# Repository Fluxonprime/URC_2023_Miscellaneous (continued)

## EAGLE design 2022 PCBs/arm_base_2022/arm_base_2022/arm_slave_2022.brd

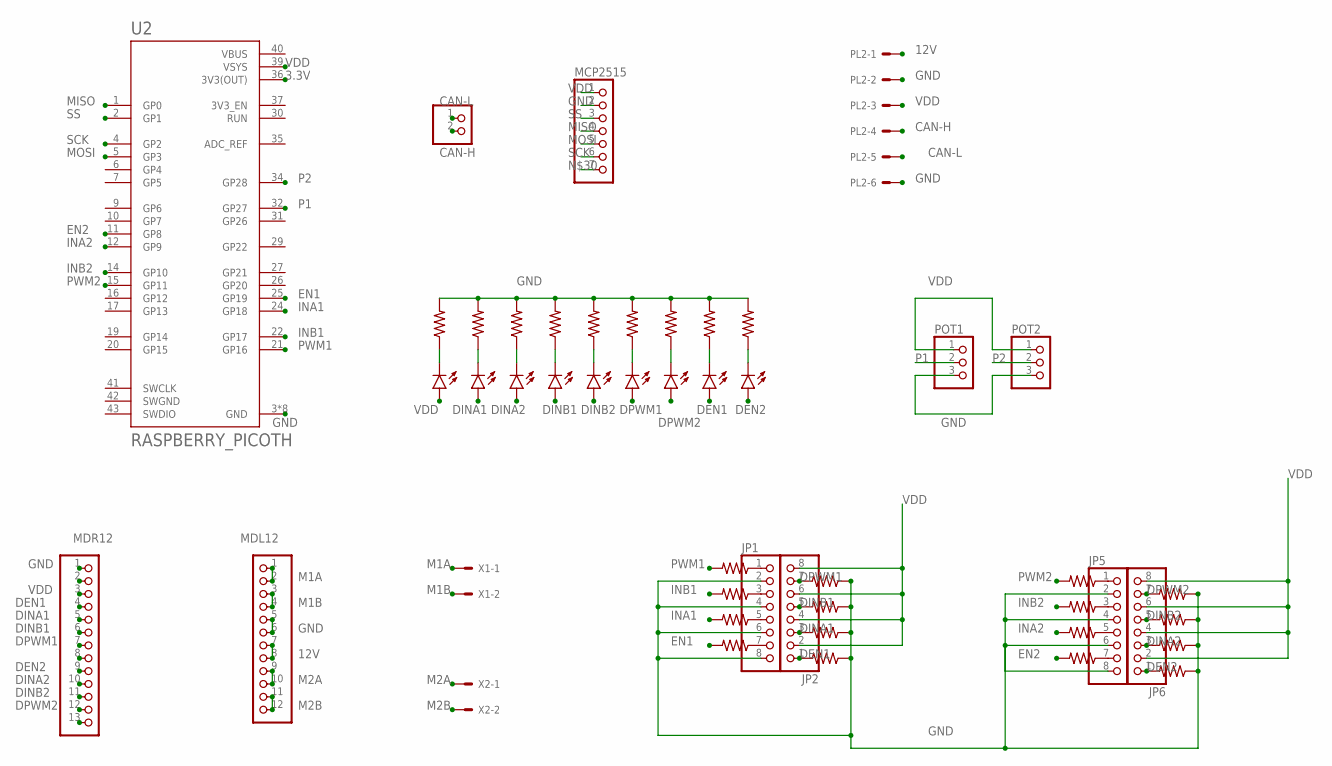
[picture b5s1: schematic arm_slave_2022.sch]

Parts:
CAN_L: CAN_H; 1X02
EN1, EN2: LEDSMT1206; 1206
INA1, INA2: LEDSMT1206; 1206
INB1, INB2: LEDSMT1206; 1206
JP1, JP2, JP5, JP6: PINHD-1X8BIG; 1X08-BIG
MCP2515: PINHD-1X7; 1X07
MDL: MDL12; 1X12
MDR: MDR12; 1X13
PL2: 555X-6V; 5566-6
POT1, POT2: PINHD-1X3; 1X03
PWM1, PWM2: LEDSMT1206; 1206
R3, R4, R5, R6, R9, R11, R14, R15, R16, R17, R18, R19, R20, R33, R34, R56, R58, R59, R60, R61, R62, R63, R64, R65, R66: R-US_R0805; R0805
U2: RASPBERRY_PICOTH; PICO-PKG-TH
VDD: LEDSMT1206; 1206
X1, X2: KK-156-2

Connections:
3.3V: U2.36 (3V3(OUT))
12V: MDL.7, MDL.8, PL2.1
CAN-H: CAN_L.2, PL2.4
CAN-L: CAN_L.1, PL2.5
DEN1: EN1.A, JP2.1, MDR.4, R11.2
DEN2: EN2.A, JP6.1, MDR.9, R58.2
DINA1: INA1.A, JP2.3, MDR.5, R4.2
DINA2: INA2.A, JP6.3, MDR.10, R6.2
DINB1: INB1.A, JP2.5, MDR.6, R9.2
DINB2: INB2.A, JP6.5, MDR.11, R56.2
DPWM1: JP2.7, MDR.7, PWM1.A, R3.2
DPWM2: JP6.7, MDR.12, PWM2.A, R5.2
EN1: R62.2, U2.25 (GP19)
EN2: R66.2, U2.11 (GP8)
GND: JP1.2, JP1.4, JP1.6, JP1.8, JP5.2, JP5.4, JP5.6, JP5.8, MCP2515.2, MDL.5, MDL.6, MDR.1, PL2.2, PL2.6, POT1.3, POT2.3, R3.1, R5.1, R14.2, R15.2, R16.2, R17.2, R18.2, R19.2, R20.2, R33.2, R34.2, U2.3 (GND), U2.8 (GND), U2.13 (GND), U2.18 (GND), U2.23 (GND), U2.28 (GND), U2.33 (GND), U2.38 (GND)
INA1: R61.2, U2.24 (GP18)
INA2: R65.2, U2.12 (GP9)
INB1: R60.2, U2.22 (GP17)
INB2: R64.2, U2.14 (GP10)
M1A: MDL.1, MDL.2, X1.1
M1B: MDL.3, MDL.4, X1.2
M2A: MDL.9, MDL.10, X2.1
M2B: MDL.11, MDL.12, X2.2
MISO: MCP2515.4, U2.1 (GP0)
MOSI: MCP2515.5, U2.5 (GP3)
unnamed: INA1.C, R15.1
unnamed: INA2.C, R16.1
unnamed: INB1.C, R17.1
unnamed: R14.1, VDD.C
unnamed: INB2.C, R18.1
unnamed: PWM1.C, R19.1
unnamed: PWM2.C, R20.1
unnamed: EN1.C, R33.1
unnamed: EN2.C, R34.1
unnamed: JP1.1, R59.1
unnamed: JP1.3, R60.1
unnamed: JP1.5, R61.1
unnamed: JP1.7, R62.1
unnamed: JP5.1, R63.1
unnamed: JP5.3, R64.1
unnamed: JP5.5, R65.1
unnamed: JP5.7, R66.1
P1: POT1.2, U2.32 (GP27)
P2: POT2.2, U2.34 (GP28)
PWM1: R59.2, U2.21 (GP16)
PWM2: R63.2, U2.15 (GP11)
SCK: MCP2515.6, U2.4 (GP2)
SS: MCP2515.3, U2.2 (GP1)
SWGND: U2.42 (SWGND)
VBUS: U2.40 (VBUS)
VDD: JP2.2, JP2.4, JP2.6, JP2.8, JP6.2, JP6.4, JP6.6, JP6.8, MCP2515.1, MDR.3, PL2.3, POT1.1, POT2.1, U2.39 (VSYS), VDD.A

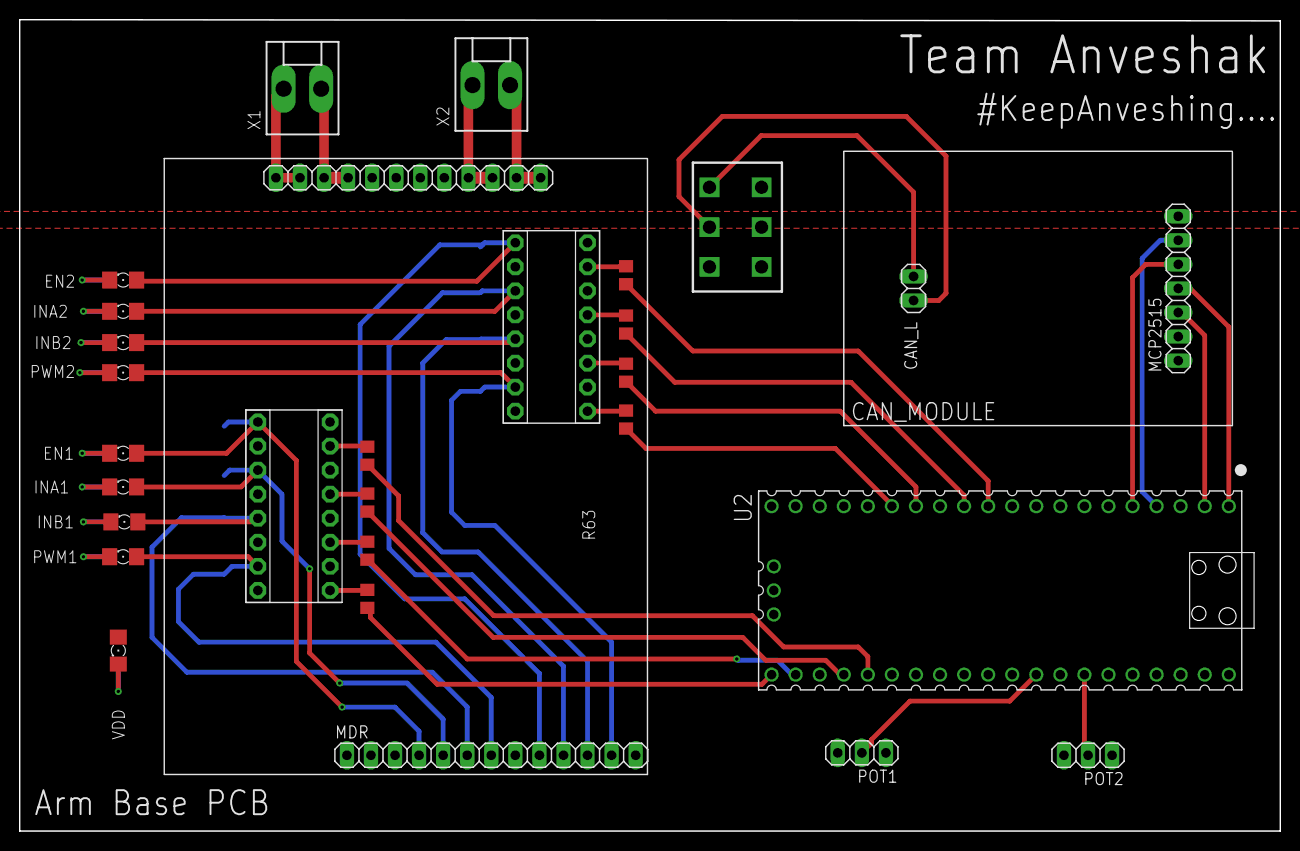
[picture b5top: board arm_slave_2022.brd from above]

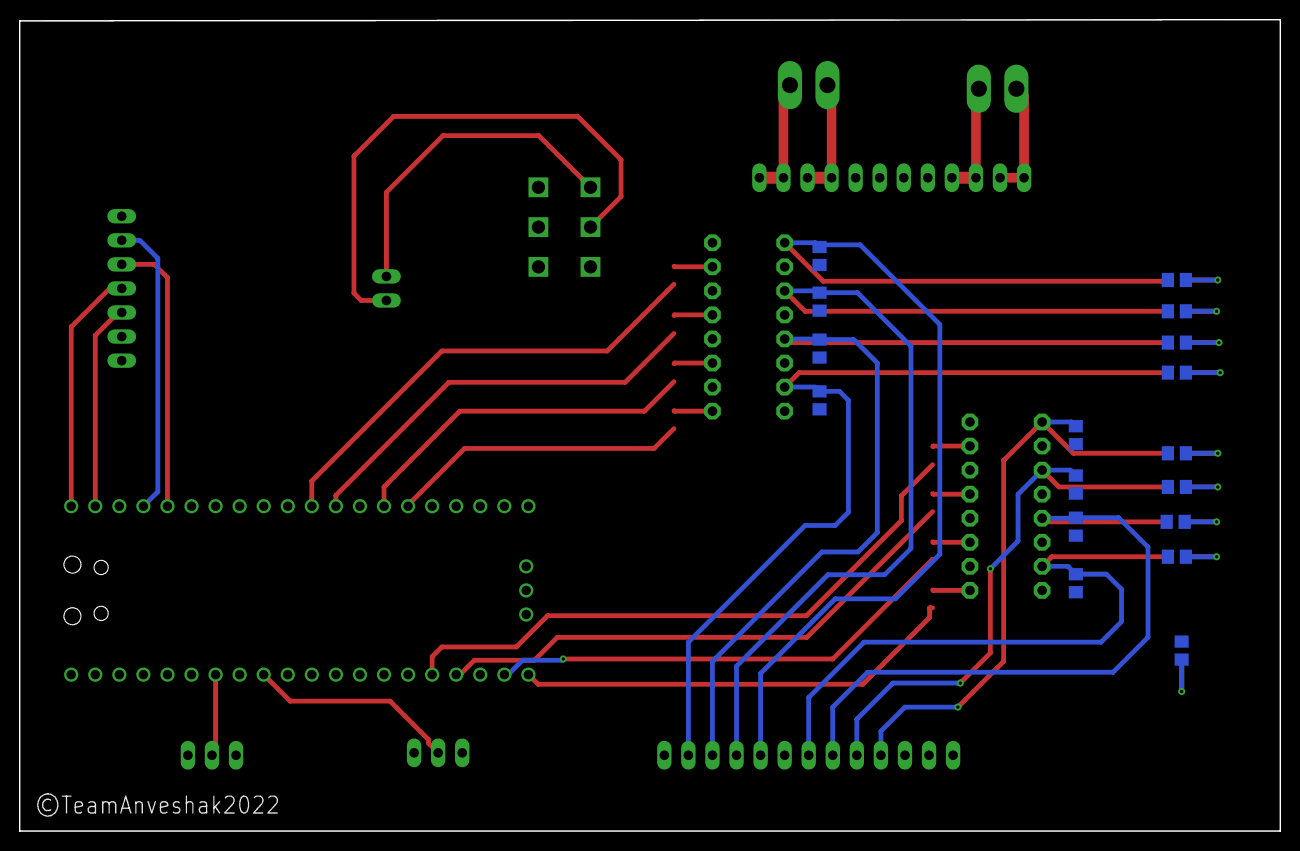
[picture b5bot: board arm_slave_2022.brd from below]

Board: 2 copper layers, 133.1 x 85.6 mm, 48 parts (17 on the bottom side), 48 nets.

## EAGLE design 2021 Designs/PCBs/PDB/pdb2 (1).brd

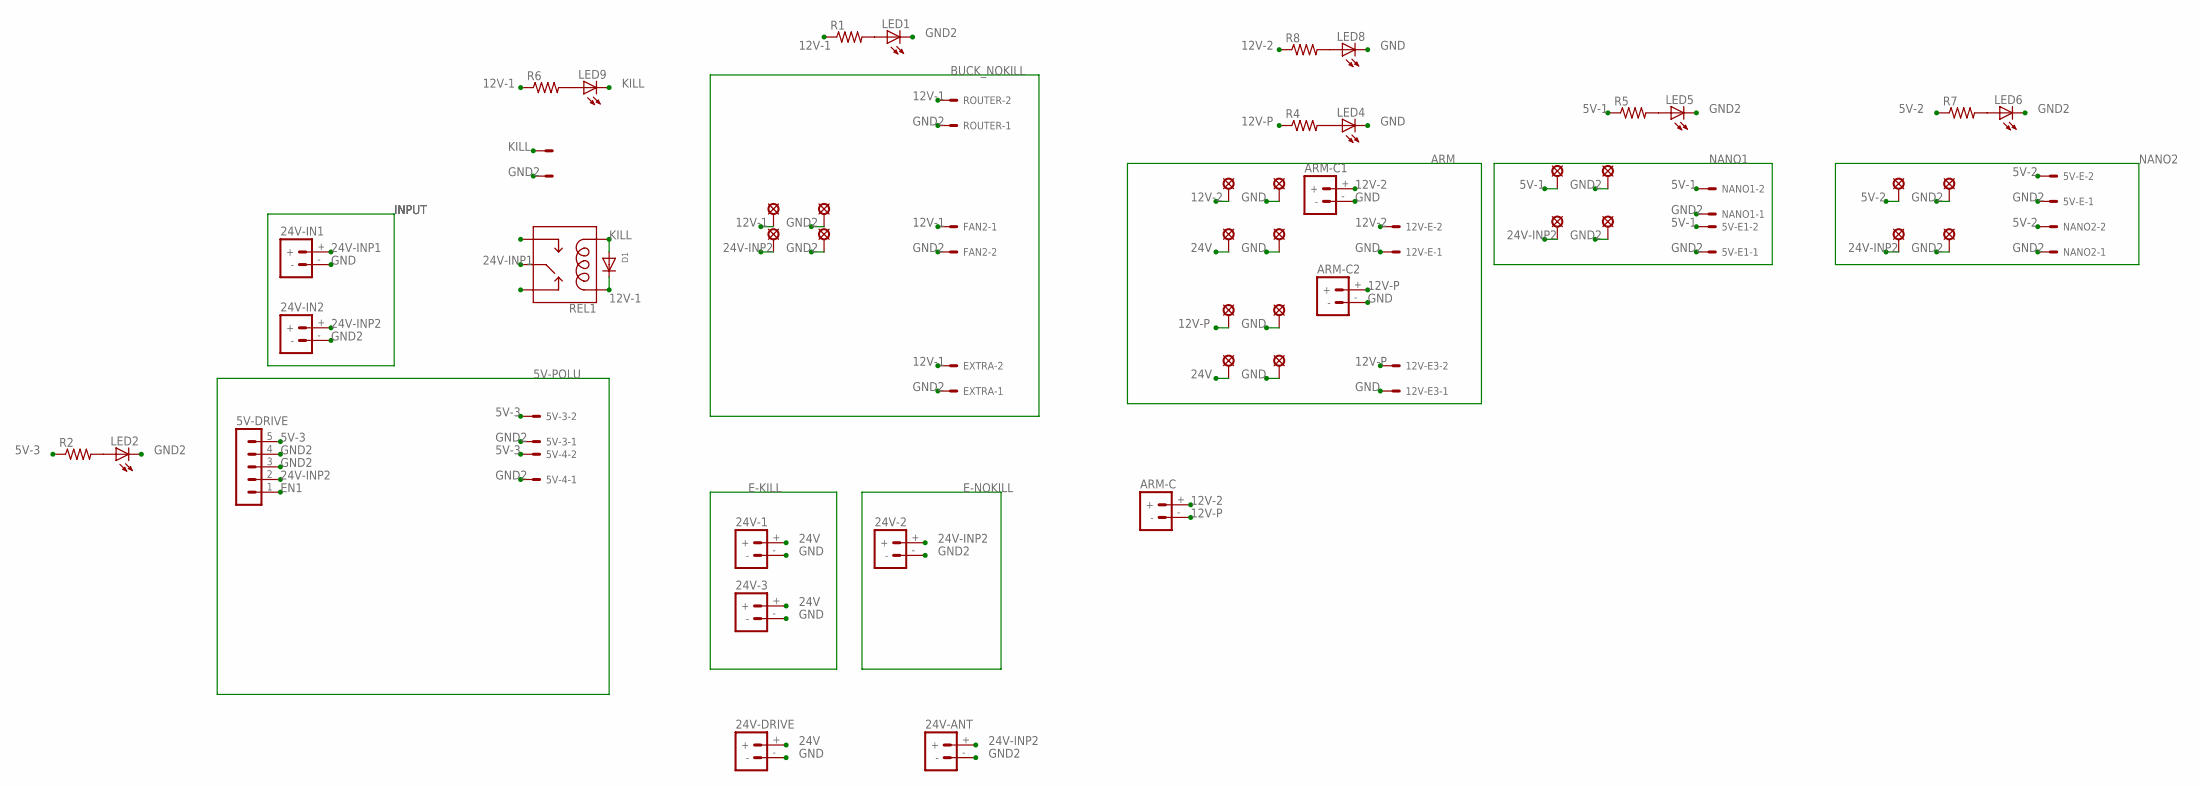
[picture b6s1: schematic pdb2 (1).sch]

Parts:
5V-3, 5V-4, 5V-E, 5V-E1, 12V-E, 12V-E3: 87758-0216; KK-156-2
5V-DRIVE: MA05-1
24V-1, 24V-2, 24V-3, 24V-ANT, 24V-DRIVE, 24V-IN1, 24V-IN2: BATTERY_CONN_DEANS; DEANS
ARM-C, ARM-C1, ARM-C2: BATTERY_CONN_DEANS; DEANS
D1: DIODEDO-1N4148; DO-1N4148
EXTRA: 87758-0216; KK-156-2
FAN2: 87758-0216; KK-156-2
KILLSWCH: 87758-0216; KK-156-2
LED1, LED2, LED4, LED5, LED6, LED8, LED9: LEDB152; Q62902-B152
LSP5, LSP6, LSP7, LSP8, LSP9, LSP10, LSP11, LSP12, LSP13, LSP14, LSP15, LSP16, LSP17, LSP18, LSP19, LSP20, LSP29, LSP30, LSP31, LSP32: LSP10
NANO1, NANO2: 87758-0216; KK-156-2
R1, R2, R4, R5, R6, R7, R8: R-US_0207/7; 0207/7
REL1: RELAY-SPDT-JQX-15F; RELAY-T90
ROUTER: 5566-2; KK-156-2

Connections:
5V-1: 5V-E1.2, LSP17.MP, NANO1.2, R5.1
5V-2: 5V-E.2, LSP29.MP, NANO2.2, R7.1
5V-3: 5V-3.2, 5V-4.2, 5V-DRIVE.5, R2.1
12V-1: D1.C, EXTRA.2, FAN2.1, LSP5.MP, R1.1, R6.1, REL1.COIL1, ROUTER.2
12V-2: 12V-E.2, ARM-C.+, ARM-C1.+, LSP10.MP, R8.1
12V-P: 12V-E3.2, ARM-C.-, ARM-C2.+, LSP13.MP, R4.1
24V: 24V-1.+, 24V-3.+, 24V-DRIVE.+, LSP9.MP, LSP15.MP, REL1.NO
24V-INP1: 24V-IN1.+, REL1.MAIN
24V-INP2: 5V-DRIVE.2, 24V-2.+, 24V-ANT.+, 24V-IN2.+, LSP8.MP, LSP19.MP, LSP31.MP
EN1: 5V-DRIVE.1
GND: 12V-E.1, 12V-E3.1, 24V-1.-, 24V-3.-, 24V-DRIVE.-, 24V-IN1.-, ARM-C1.-, ARM-C2.-, LED4.K (C), LED8.K (C), LSP11.MP, LSP12.MP, LSP14.MP, LSP16.MP
GND2: 5V-3.1, 5V-4.1, 5V-DRIVE.3, 5V-DRIVE.4, 5V-E.1, 5V-E1.1, 24V-2.-, 24V-ANT.-, 24V-IN2.-, EXTRA.1, FAN2.2, KILLSWCH.2, LED1.K (C), LED2.K (C), LED5.K (C), LED6.K (C), LSP6.MP, LSP7.MP, LSP18.MP, LSP20.MP, LSP30.MP, LSP32.MP, NANO1.1, NANO2.1, ROUTER.1
KILL: D1.A, KILLSWCH.1, LED9.K (C), REL1.COIL2
unnamed: LED2.A, R2.2
unnamed: LED4.A, R4.2
unnamed: LED5.A, R5.2
unnamed: LED9.A, R6.2
unnamed: LED6.A, R7.2
unnamed: LED8.A, R8.2
unnamed: LED1.A, R1.2

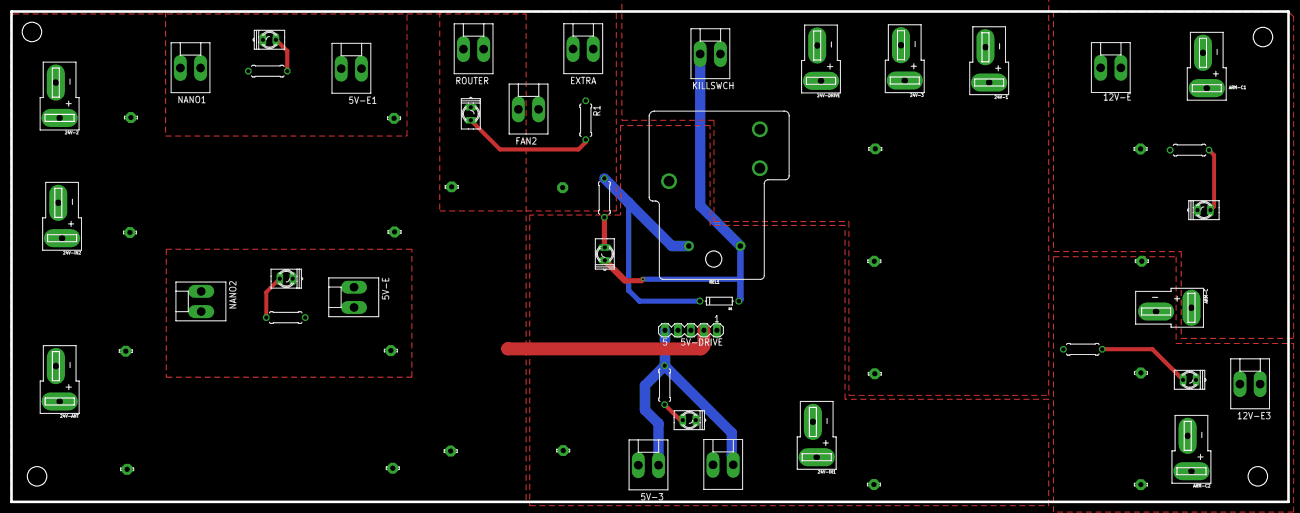
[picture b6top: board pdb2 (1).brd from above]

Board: 2 copper layers, 250.0 x 96.0 mm, 59 parts (1 on the bottom side), 19 nets.

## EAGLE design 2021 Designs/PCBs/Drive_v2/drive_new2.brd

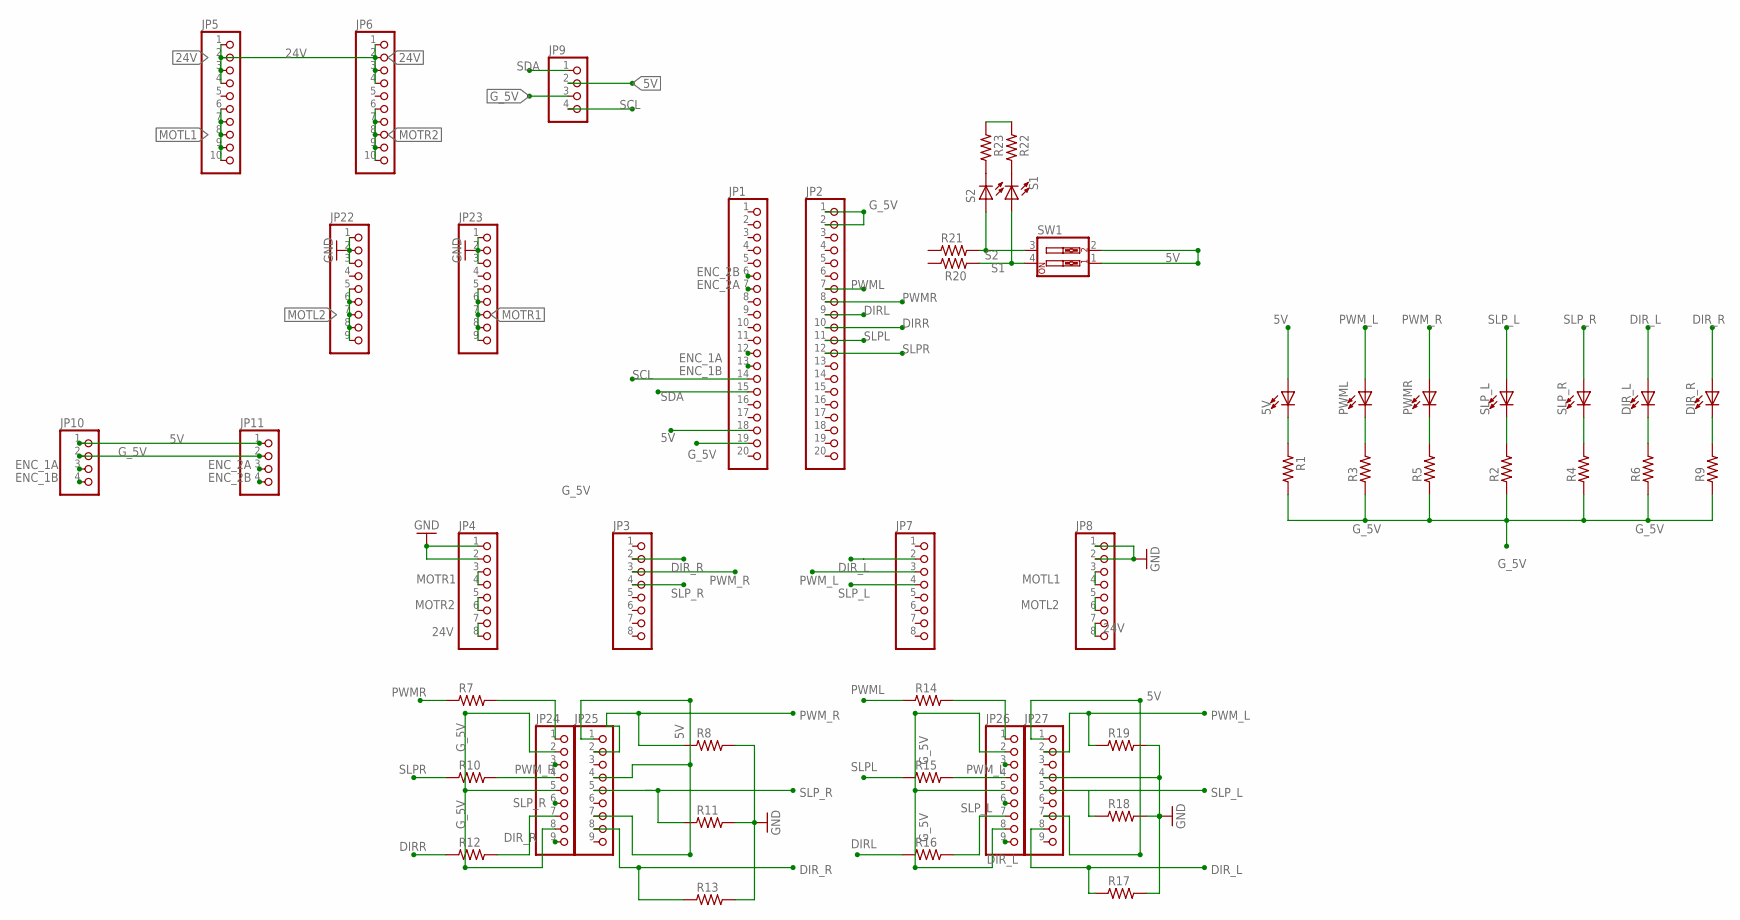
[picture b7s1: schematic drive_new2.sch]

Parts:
5V: RED; LED_1206
DIR_L: BLUE; LED_1206
DIR_R: BLUE; LED_1206
JP1, JP2: PINHD-1X20; 1X20
JP3, JP4, JP7, JP8: PINHD-1X8; 1X08
JP5, JP6: PINHD-1X10; 1X10
JP9, JP10, JP11: PINHD-1X4; 1X04
JP22, JP23, JP24, JP25, JP26, JP27: PINHD-1X9; 1X09
PWML: RED; LED_1206
PWMR: RED; LED_1206
R1, R2, R3, R4, R5, R6, R7, R8, R9, R10, R11, R12, R13, R14, R15, R16, R17, R18, R19, R20, R21, R22, R23: R_0805; R0805
S1, S2: RED; LED_1206
SLP_L: BLUE; LED_1206
SLP_R: BLUE; LED_1206
SW1: SW_DIP-2; EDG-02

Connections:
5V: 5V.A, JP1.18, JP9.2, JP10.1, JP11.1, JP25.1, JP25.4, JP25.7, JP27.1, JP27.7, SW1.1, SW1.2
24V: JP4.7, JP4.8, JP5.1, JP5.2, JP5.3, JP5.4, JP6.1, JP6.2, JP6.3, JP6.4, JP8.7, JP8.8
DIRL: JP2.9, R16.1
DIRR: JP2.10, R12.1
DIR_L: DIR_L.A, JP7.2, JP26.9, JP27.8, R17.1
DIR_R: DIR_R.A, JP3.2, JP24.9, JP25.8, R13.1
ENC_1A: JP1.12, JP10.3
ENC_1B: JP1.13, JP10.4
ENC_2A: JP1.7, JP11.3
ENC_2B: JP1.6, JP11.4
GND: JP4.1, JP4.2, JP8.1, JP8.2, JP22.1, JP22.2, JP22.3, JP23.1, JP23.2, JP23.3, JP27.4, R8.2, R11.2, R13.2, R17.2, R18.2, R19.2
G_5V: JP1.19, JP2.1, JP2.2, JP9.3, JP10.2, JP11.2, JP24.2, JP24.5, JP24.8, JP26.2, JP26.5, JP26.8, R1.2, R2.1, R3.1, R4.1, R5.1, R6.1, R9.1, R22.1, R23.1
MOTL1: JP5.6, JP5.7, JP5.8, JP5.9, JP5.10, JP8.3, JP8.4
MOTL2: JP8.5, JP8.6, JP22.5, JP22.6, JP22.7, JP22.8, JP22.9
MOTR1: JP4.3, JP4.4, JP23.5, JP23.6, JP23.7, JP23.8, JP23.9
MOTR2: JP4.5, JP4.6, JP6.6, JP6.7, JP6.8, JP6.9, JP6.10
unnamed: DIR_R.C, R9.2
unnamed: DIR_L.C, R6.2
unnamed: R4.2, SLP_R.C
unnamed: R2.2, SLP_L.C
unnamed: JP24.4, R10.2
unnamed: JP26.4, R15.2
unnamed: PWMR.C, R5.2
unnamed: PWML.C, R3.2
unnamed: 5V.C, R1.1
unnamed: JP24.1, R7.2
unnamed: R22.2, S1.C
unnamed: JP24.7, R12.2
unnamed: R23.2, S2.C
unnamed: JP26.1, R14.2
unnamed: JP26.7, R16.2
PWML: JP2.7, R14.1
PWMR: JP2.8, R7.1
PWM_L: JP7.3, JP26.3, JP27.2, PWML.A, R19.1
PWM_R: JP3.3, JP24.3, JP25.2, PWMR.A, R8.1
S1: R20.1, S1.A, SW1.4
S2: R21.1, S2.A, SW1.3
SCL: JP1.14, JP9.4
SDA: JP1.15, JP9.1
SLPL: JP2.11, R15.1
SLPR: JP2.12, R10.1
SLP_L: JP7.4, JP26.6, JP27.5, R18.1, SLP_L.A
SLP_R: JP3.4, JP24.6, JP25.5, R11.1, SLP_R.A

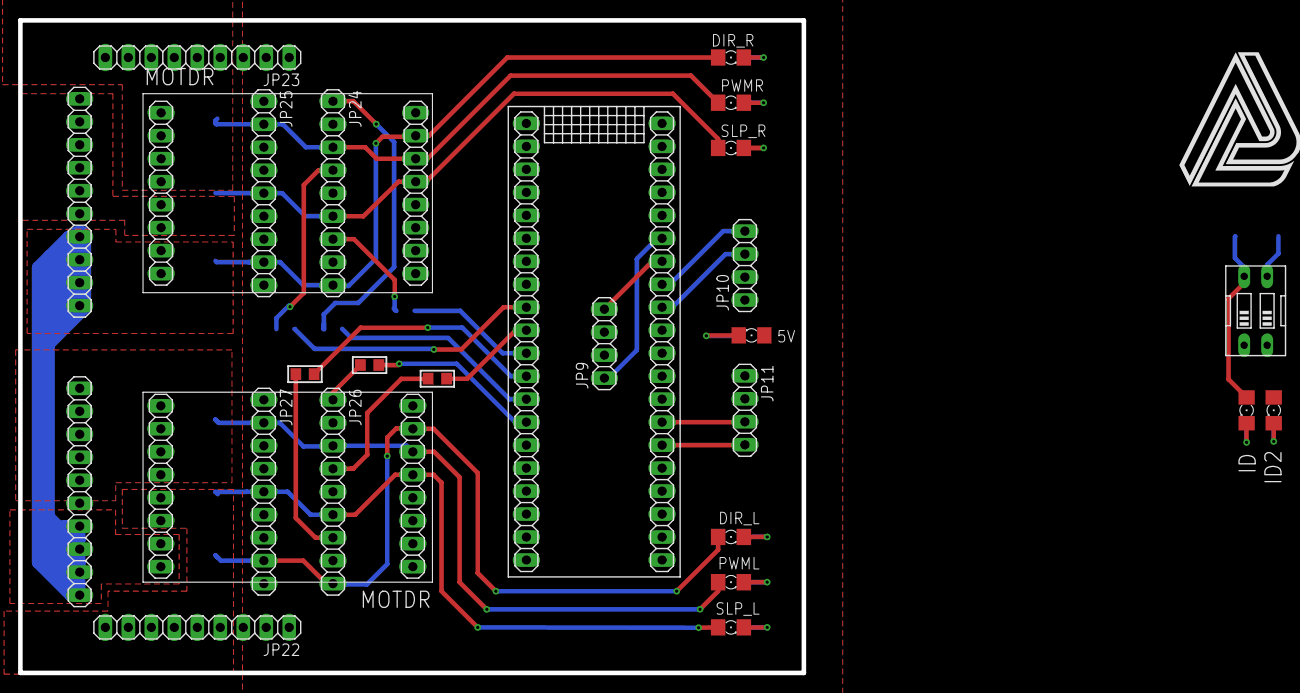
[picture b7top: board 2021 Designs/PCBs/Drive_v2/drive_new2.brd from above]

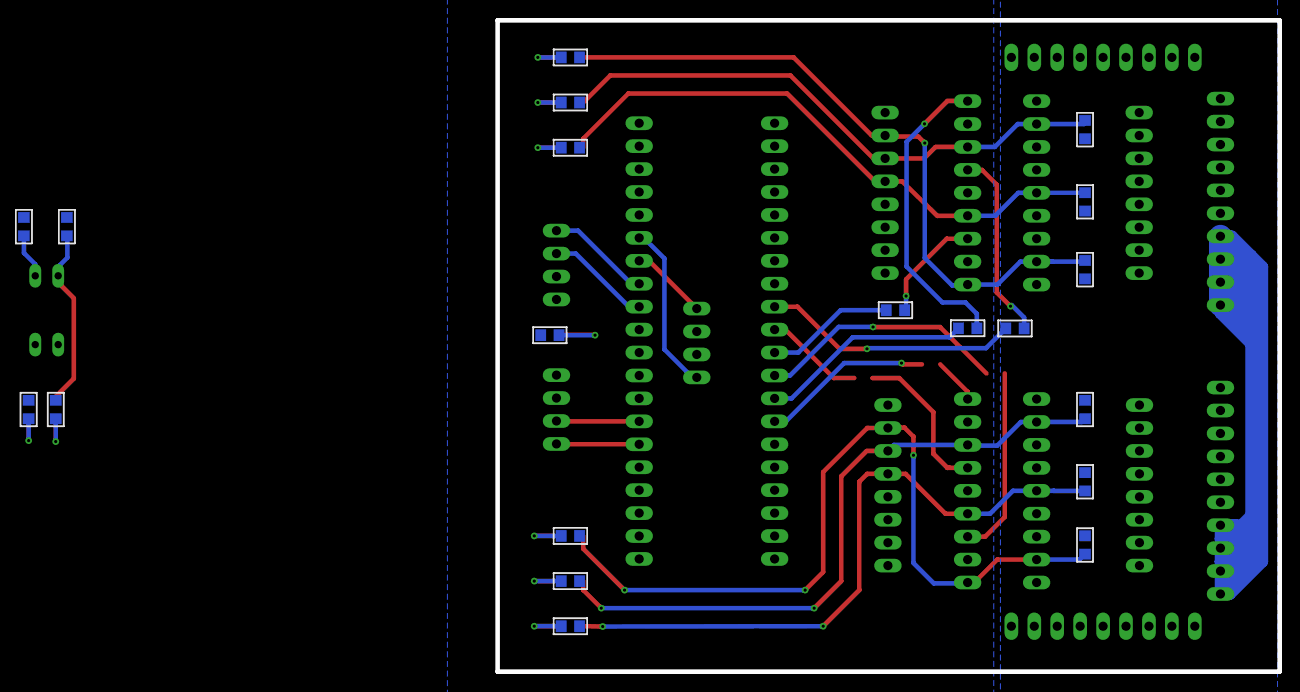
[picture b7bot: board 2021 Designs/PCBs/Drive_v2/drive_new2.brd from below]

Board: 2 copper layers, 86.6 x 72.1 mm, 50 parts (20 on the bottom side), 43 nets.

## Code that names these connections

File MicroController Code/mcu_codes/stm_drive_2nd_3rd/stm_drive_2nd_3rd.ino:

//HardwareTimer timer(3);

#include <Wire.h>

/////
int address = 15;   //change address here 15,16,17
/////
#define LED_BUILTIN PC13
#define CSr PA2
#define CSl PA3
#define slpr PA4
#define slpl PA5
#define DIRr PA1
#define DIRl PA7
#define PWMr PB0
#define PWMl PB1


int vel1 ,vel2 , om1 ,om2 = 0, hb =0;
int pwmr = 0, pwml = 0;
int vel,omega=0;

void receiveEvent(int howMany)
{
  if ( Wire.available())
  {
    vel1 = Wire.read();
    //vel2 = Wire.read();
    om1 = Wire.read();
    //om2 = Wire.read();
    hb = Wire.read();
    
    //vel = vel1 + (vel2<<8);
    //omega = om1 + (om2<<8);
    
    vel=vel1-127;
    omega=om1-127;	  
	
  }
}

void setup()
{ Serial.end();
  pinMode(PA11, OUTPUT);
  //timer.setPrescaleFactor(32);
  //timer.setOverflow(127);
  //timer.refresh();
  

  pinMode(PWMl, OUTPUT);
  pinMode(PWMr, OUTPUT);
  pinMode(slpl, OUTPUT);
  pinMode(slpr, OUTPUT);
  pinMode(DIRr, OUTPUT);
  pinMode(DIRl, OUTPUT);
  pinMode(CSr, INPUT);
  pinMode(CSl, INPUT);

  digitalWrite(slpl, HIGH);
  digitalWrite(slpr, HIGH);

  pinMode(PC13, OUTPUT);
  digitalWrite(PC13, HIGH);

  Wire.begin(address);

  Wire.onReceive(receiveEvent);

 //pwmWrite(PWMl, 0);
  //pwmWrite(PWMr,0);
  digitalWrite(slpl, LOW);
  digitalWrite(slpr,LOW);
  digitalWrite(DIRr, LOW);
  digitalWrite(DIRl, LOW);

}

#define analogMax 255
void loop()
{
//  analogWriteFrequency(17000);
  pwmr = int(vel+omega)*255/110;
  pwml = int(vel-omega)*255/110;
  if (pwmr>255) 
    pwmr = 255;
   else if (pwmr<-255)
    pwmr = -255;
  if (pwml>255) 
    pwml = 255;
   else if (pwml<-255)
    pwml = -255;

  if (hb==0)
  {
	  if (pwmr > 0)
	  {
	    digitalWrite(slpr, HIGH);
	    digitalWrite(DIRr, HIGH);
	    analogWrite(PWMr, abs(pwmr));
      
	  }
	  else if (pwmr < 0)
	  {
	    digitalWrite(slpr, HIGH);
	    digitalWrite(DIRr, LOW);
	    analogWrite(PWMr, abs(pwmr));
      digitalWrite(PC13,LOW);
      delay(100);
      digitalWrite(PC13,HIGH);
      delay(100);
	  }
	  else
	  {
	    digitalWrite(slpr, LOW);
      digitalWrite(DIRr,LOW);
	    analogWrite(PWMr, 0);
     digitalWrite(PC13,LOW);
      delay(100);
	  }

	  if (pwml > 0)
	  {
	    digitalWrite(slpl, HIGH);
	    digitalWrite(DIRl, LOW);
	    analogWrite(PWMl, abs(pwml));
	  }
	  else if (pwml < 0)
	  {
	    digitalWrite(slpl, HIGH);
	    digitalWrite(DIRl, HIGH);
	    analogWrite(PWMl, abs(pwml));
      digitalWrite(PC13,LOW);
      delay(100);
      digitalWrite(PC13,HIGH);
      delay(100);
	  }
	  else
	  {
	    digitalWrite(slpl, LOW);
      digitalWrite(DIRl, LOW);
	    analogWrite(PWMl, 0);
	  }
  }
  else
  {
  	digitalWrite(slpr, LOW);
	analogWrite(PWMr, 0);
	digitalWrite(slpl, LOW);
	analogWrite(PWMl, 0);
  }

  // give PWM time to properly write
  delay (10);

}

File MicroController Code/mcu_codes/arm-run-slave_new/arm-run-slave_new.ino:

// NOTE all outputs are ACTIVE LOW

//HardwareTimer timer(3);

#include <stdlib.h>

#include <mcp_can.h>
#include <SPI.h>

#define SPI_CS_PIN 17
MCP_CAN CAN (SPI_CS_PIN);


#define LED 25

#define PWM1 15
#define INB1 14
#define INA1 13
#define EN1  12

#define PWM2 11
#define INB2 10
#define INA2 9
#define EN2  8

#define PWM3 7
#define INB3 6
#define INA3 5
#define EN3  4

#define PWM4 3
#define INB4 2
#define INA4 1
#define EN4  0



#define PWMMAX 0xFFF

void initAndClearOutputs ();
void fixPWM ();
void initCAN ();
void updatePinBuff ();
void writeMotors ();

// for CAN
#define STD_FRAME 0
const   unsigned long SELF_ID = 0xF1;

#define LOST_COMM_INTERVAL 2000
unsigned long last_comm_time = 0;
unsigned long curr_time = 0;

// PWM, EN, INA, INB (in that order)
uint8_t buff[16] = {0, 0, 0, 0, 0, 0, 0, 0,0,0,0,0,0,0,0,0};

void setup () {
  //fixPWM ();
  
  writeMotors();
  initAndClearOutputs ();
  initCAN();

  curr_time = millis();
  last_comm_time = curr_time;
}

void loop () {
  curr_time = millis();
  if (CAN_MSGAVAIL == CAN.checkReceive())
  {
    Serial.println("received");
    unsigned char len;
    unsigned char tmp[8];
    CAN.readMsgBuf (&len, tmp);
    if (CAN.getCanId() == SELF_ID)
    {
      for (int i = 0; i < 4; i++)
        buff[4*i] = tmp[i];

       for (int i=4;i<8;i++)
       {
        buff[4*(i-4)+1] = tmp[i]&1;
        buff[4*(i-4)+2] = (tmp[i]>>1)&1;
        buff[4*(i-4)+3] = (tmp[i]>>2)&1;
        
       }
      last_comm_time = curr_time;
      digitalWrite (LED, HIGH);
    }
    last_comm_time = curr_time;
  }
  
  if (curr_time - last_comm_time > LOST_COMM_INTERVAL)
  {
    for (int i = 0; i < 16; i++)
      buff[i] = 0;
    last_comm_time = curr_time;
    digitalWrite (LED, LOW);
  }

  writeMotors();
}




void writeMotors () {

  analogWriteResolution(12);
  



  
  // motor_buff in this order: pwm, en, ina, inb
  analogWrite (PWM1,    (buff[0]*0x3FF)/0xFF);
  digitalWrite (EN1,  buff[1]);
  digitalWrite (INA1, buff[3]);
  digitalWrite (INB1, buff[2]);
  analogWrite (PWM2,    (buff[4]*0xFFF)/0xFF);
  digitalWrite (EN2,  buff[5]);
  digitalWrite (INA2, buff[6]);
  digitalWrite (INB2, buff[7]);
  analogWrite (PWM3,    (buff[8]*0xFFF)/0xFF);
  digitalWrite (EN3,  buff[9]);
  digitalWrite (INA3, buff[10]);
  digitalWrite (INB3, buff[11]);
  digitalWrite (PWM4, buff[13]);
  analogWrite (EN4,    (buff[12]*0xFFF)/0xFF);
  digitalWrite (INA4, buff[15]);
  digitalWrite (INB4, buff[14]);
}

/*void fixPWM() {
  //timer.setPrescaleFactor(4);
  //timer.setOverflow(1024);
  //timer.refresh();
}*/

void initCAN () {
  Serial.begin(500000);
  digitalWrite (LED, LOW);

  while (CAN_OK != CAN.begin(CAN_500KBPS))
  {
      digitalWrite (LED, HIGH);
      delay (500);
      digitalWrite (LED, LOW);
      delay (500);
  }
  
  digitalWrite (LED, HIGH);
  delay(1000);
  digitalWrite (LED, LOW);
  delay(1000);
  digitalWrite (LED, HIGH);
  delay(1000);
  Serial.println("CAN Working");
  delay(500);
}

void initAndClearOutputs () {
  pinMode (LED, OUTPUT);
  pinMode (PWM1, OUTPUT);
  pinMode (INB1, OUTPUT);
  pinMode (INA1, OUTPUT);
  pinMode (EN1, OUTPUT);
  pinMode (PWM2, OUTPUT);
  pinMode (INB2, OUTPUT);
  pinMode (INA2, OUTPUT);
  pinMode (EN2, OUTPUT);
  pinMode (PWM3, OUTPUT);
  pinMode (INB3, OUTPUT);
  pinMode (INA3, OUTPUT);
  pinMode (EN3, OUTPUT);
  pinMode (PWM4, OUTPUT);
  pinMode (INB4, OUTPUT);
  pinMode (INA4, OUTPUT);
  pinMode (EN4, OUTPUT);

  analogWriteResolution(12);
  

  digitalWrite (LED, HIGH);
  analogWrite (PWM1, PWMMAX);
  digitalWrite (INB1, HIGH);
  digitalWrite (INA1, HIGH);
  digitalWrite (EN1, HIGH);
  digitalWrite (PWM2, PWMMAX);
  digitalWrite (INB2, HIGH);
  digitalWrite (INA2, HIGH);
  digitalWrite (EN2, HIGH);
  analogWrite (PWM3, PWMMAX);
  digitalWrite (INB3, HIGH);
  digitalWrite (INA3, HIGH);
  digitalWrite (EN3, HIGH);
  digitalWrite (PWM4, HIGH);
  digitalWrite (INB4, HIGH);
  digitalWrite (INA4, HIGH);
  analogWrite (EN4, PWMMAX);
}

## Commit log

2023-07-14 Uploading For Later use
